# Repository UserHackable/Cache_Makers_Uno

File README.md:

## The Cache Makers Uno project

I created this board in the hopes of using it to teach a group of kids in the [Cache Makers](cachemakers.org) 4H program. 

The build met with mixed success. The board has a large number of solder points to solder in. The older students with a little more hand eye coordination and practice with soldering did ok, the Younger students struggled quite a bit more. 
The board, when completed does provide a functional Arduino Uno compatible device, with some extras for convenience when playing around beginning arduino programming. 

For the next session, I used the [YourDuino RoboRED](http://yourduino.com/sunshop2/index.php?l=product_detail&p=429) which I am a fan of. 
## CacheMakerUno 

### Board dimensions

* (220000, 220068) original units
* (2.2000, 2.2007) inches
* (55.8800, 55.8973) mm

| Front | Back |
| --- | --- |
|  |  |

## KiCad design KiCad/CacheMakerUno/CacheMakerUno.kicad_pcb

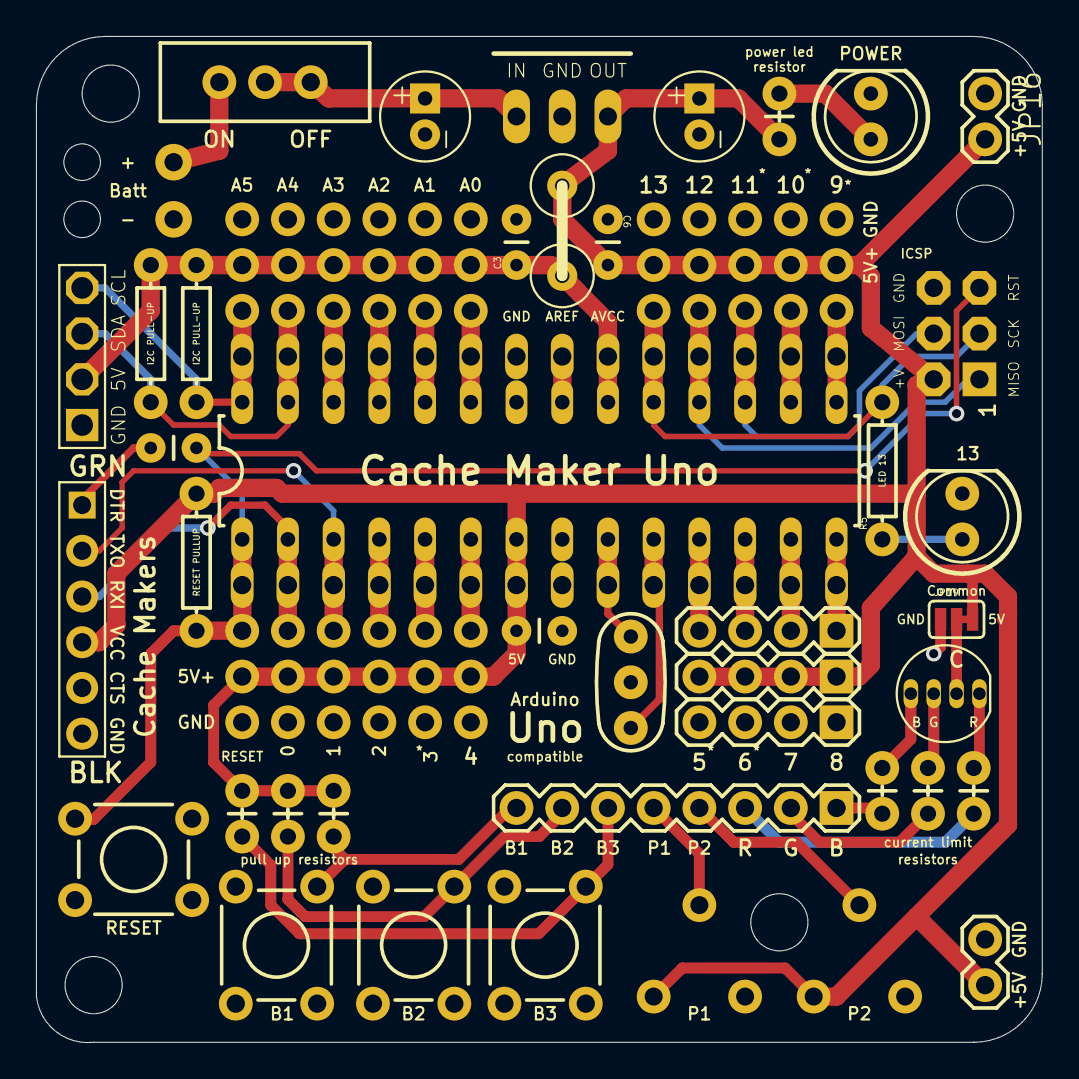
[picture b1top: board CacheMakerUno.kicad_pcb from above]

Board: 2 copper layers, 55.9 x 55.9 mm, 58 parts (0 on the bottom side), 43 nets.

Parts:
C1, C2, C3, C6: CAP-PTH-SMALL
C4, C5: CAP-PTH-2MM
D2: LED-RGB-CA-THRUDIFFUSE; LED-RGB-THRU
GND0: M1; M1_NO_STRAIN
IC1: TO-220-REG-BASIC
J1: AVR_SPI_PRG_6LABELED; 2X3-NS
JP1, JP3, JP6: 1X05_NO_SILK
JP2: FTDI_DEVICE; FTDI_DEVICE_SIDE
JP4, JP5: M14HEADER; 1X14-HEADER
JP7, JP8, JP9, JP10, JP11, JP12: 1X06
JP13, JP14, JP15: 1X04
JP16, JP17: M02PTH; 1X02
JP18: 1X08
JP19: JUMPER-3SMD; SJ_3
LED1, LED2: LED5MM
R1, R2, R3, R5: AXIAL-0.3
R4, R6, R7, R8, R9, R10, R11: AXIAL-0.1
RV1, RV2: TRIM_POT
S1, S2, S3, S5: TACTILE-PTH
S4: SWITCH-SPDT
U1: ATMEGA328P_PDIP; DIL28-3
U$1: LFB; ALFB-01
U$2: I2C
UNK_HOLE_0: dummyfp0
UNK_HOLE_1: dummyfp1
UNK_HOLE_2: dummyfp2
UNK_HOLE_3: dummyfp3
V+0: M1; M1_NO_STRAIN
Y1: RESONATOR-PTH

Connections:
5V: C1.1, C4.+, C6.2, D2.2, IC1.3, J1.2, JP2.P$4, JP3.1, JP3.2, JP3.3, JP3.4, JP3.5, JP4.8, JP8.1, JP8.2, JP8.3, JP8.4, JP8.5, JP8.6, JP14.1, JP14.2, JP14.3, JP14.4, JP16.2, JP17.2, JP19.2, JP19.3, R1.P$2, R4.P$2, R9.P$1, R10.P$1, R11.P$1, RV1.2, RV2.2, U1.7, U$1.1
A0: JP5.9, JP7.1, U1.23
A1: JP5.10, JP7.2, U1.24
A2: JP5.11, JP7.3, U1.25
A3: JP5.12, JP7.4, U1.26
A4: JP5.13, JP7.5, R2.P$2, U1.27, U$2.SDA
A5: JP5.14, JP7.6, R3.P$1, U1.28, U$2.SCL
AREF: JP5.7, U1.21
AVCC: C3.1, JP5.6, JP11.1, JP11.2, JP11.3, JP11.4, JP11.5, JP11.6, R2.P$1, R3.P$2, U1.20, U$1.2, U$2.5V
B1: JP18.8, R9.P$2, S1.4
B2: JP18.7, R10.P$2, S2.4
B3: JP18.6, R11.P$2, S3.4
BLUE: JP18.1, R8.P$1
D2: JP4.11, JP10.3, U1.4
D3: JP4.10, JP10.2, U1.5
D4: JP4.9, JP10.1, U1.6
D5: JP4.4, JP13.4, U1.11
D6: JP4.3, JP13.3, U1.12
D7: JP4.2, JP13.2, U1.13
D8: JP4.1, JP13.1, U1.14
D9: JP1.1, JP5.1, U1.15
D10: JP1.2, JP5.2, U1.16
D11: J1.4, JP1.3, JP5.3, U1.17
D12: J1.1, JP1.4, JP5.4, U1.18
D13: J1.3, JP1.5, JP5.5, R5.P$2, U1.19
DTR: C2.1, JP2.P$1
GND: C1.2, C3.2, C4.-, C5.-, C6.1, GND0.P$1, IC1.2, J1.6, JP2.P$5, JP2.P$6, JP4.7, JP5.8, JP6.1, JP6.2, JP6.3, JP6.4, JP6.5, JP9.1, JP9.2, JP9.3, JP9.4, JP9.5, JP9.6, JP12.1, JP12.2, JP12.3, JP12.4, JP12.5, JP12.6, JP15.1, JP15.2, JP15.3, JP15.4, JP16.1, JP17.1, JP19.1, LED1.K, LED2.K, RV1.3, RV2.3, S1.2, S2.2, S3.2, S5.1, S5.2, U1.8, U1.22, U$2.GND, Y1.2
GREEN: JP18.2, R7.P$1
unnamed: LED1.A, R4.P$1
unnamed: LED2.A, R5.P$1
unnamed: D2.1, R6.P$2
unnamed: D2.3, R7.P$2
unnamed: D2.4, R8.P$2
POT1: JP18.5, RV1.1
POT2: JP18.4, RV2.1
RED: JP18.3, R6.P$1
RESET: C2.2, J1.5, JP4.14, JP10.6, R1.P$1, S5.4, U1.1
RX0: JP2.P$3, JP4.13, JP10.5, U1.2
TX1: JP2.P$2, JP4.12, JP10.4, U1.3
VIN: C5.+, IC1.1, S4.2, S4.3
V_BATT: S4.1, V+0.P$1
XTAL1: JP4.6, U1.9, Y1.1
XTAL2: JP4.5, U1.10, Y1.3

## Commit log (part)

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2016-04-08 from Makefile
